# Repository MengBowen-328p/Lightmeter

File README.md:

# CW32_Lightmeter

# Timeline

## 2023.9.2:Finished SCH
## 2023.9.4:Finished PCB Layout

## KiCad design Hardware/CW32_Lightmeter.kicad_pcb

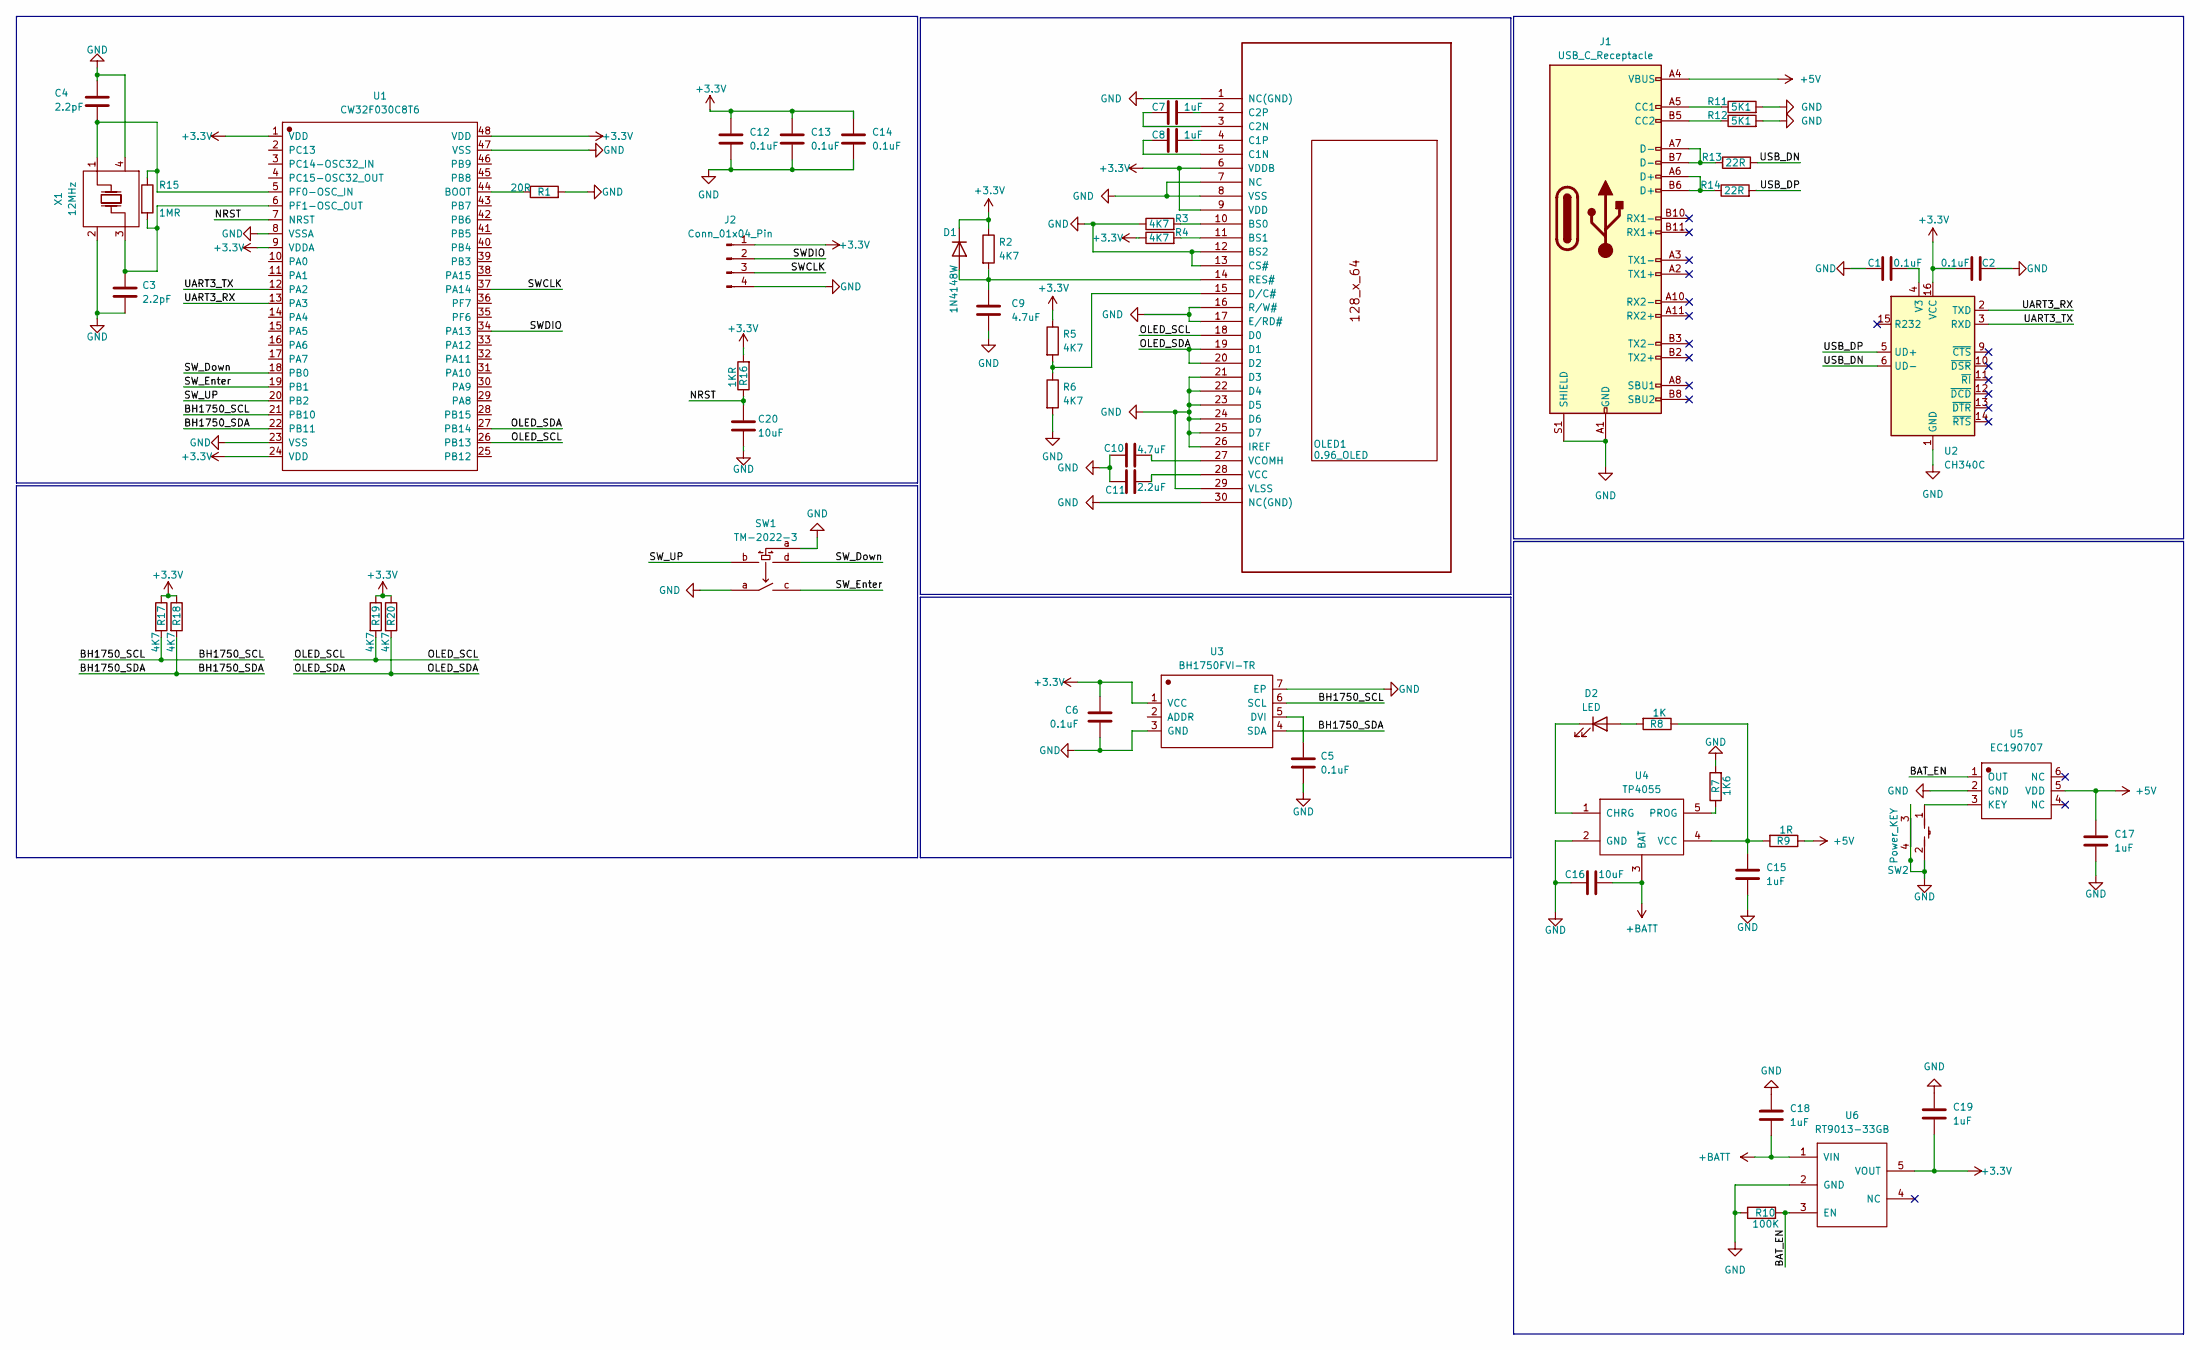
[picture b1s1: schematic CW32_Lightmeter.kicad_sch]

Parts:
C1, C2, C5, C6, C12, C13, C14: 0.1uF; C_0603_1608Metric
C3, C4: 2.2pF; C_0603_1608Metric
C7, C8, C15, C17, C18, C19: 1uF; C_0603_1608Metric
C9, C10: 4.7uF; C_0603_1608Metric
C11: 2.2uF; C_0603_1608Metric
C16, C20: 10uF; C_0603_1608Metric
D1: 1N4148W; D_SOD-123
D2: LED; LED_0603_1608Metric
J1: USB_C_Receptacle; USB_C_Receptacle_GCT_USB4105-xx-A_16P_TopMnt_Horizontal
J2: Conn_01x04_Pin; SWD_Port
OLED1: 0.96_OLED; OLED_0.96-30P-P0.70-12864
R1: 20R; R_0603_1608Metric
R2, R3, R4, R5, R6, R17, R18, R19, R20: 4K7; R_0603_1608Metric
R7: 1K6; R_0603_1608Metric
R8: 1K; R_0603_1608Metric
R9: 1R; R_0603_1608Metric
R10: 100K; R_0603_1608Metric
R11, R12: 5K1; R_0603_1608Metric
R13, R14: 22R; R_0603_1608Metric
R15: 1MR; R_0603_1608Metric
R16: 1KR; R_0603_1608Metric
SW1: TM-2022-3; SW-SMD_TM-2022-3
SW2: Power_KEY; SW-SMD_2X4X3.5MM
U1: CW32F030C8T6; LQFP-48_L7.0-W7.0-P0.50-LS9.0-BL
U2: CH340C; SOIC-16_3.9x9.9mm_P1.27mm
U3: BH1750FVI-TR; WSOF-6_L2.6-W1.6-P0.50-TL-EP
U4: TP4055; SOT-23-5_L3.0-W1.7-P0.95-LS2.8-BR
U5: EC190707; PG-SOT23-6_L2.9-W1.6-P0.95-LS2.8-BR
U6: RT9013-33GB; SOT-23-5_L3.0-W1.7-P0.95-LS2.8-BL
X1: 12MHz; CRYSTAL-SMD_4P-L3.2-W2.5-BL

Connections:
+3.3V: C2.2, C6.2, C12.1, C13.1, C14.1, C19.2, D1.1 (K), J2.1, OLED1.6 (VDDB), OLED1.9 (VDD), R2.1, R4.1, R5.1, R16.2, R17.1, R18.1, R19.1, R20.1, U1.1 (VDD), U1.9 (VDDA), U1.24 (VDD), U1.48 (VDD), U2.16 (VCC), U3.1 (VCC), U6.5 (VOUT)
+5V: C17.1, J1.A4 (VBUS), J1.A9 (VBUS), J1.B4 (VBUS), J1.B9 (VBUS), R9.1, U5.5 (VDD)
+BATT: C16.2, C18.2, U4.3 (BAT), U6.1 (VIN)
/BAT_EN: R10.2, U5.1 (OUT), U6.3 (EN)
/BH1750_SCL: R17.2, U1.21 (PB10), U3.6 (SCL)
/BH1750_SDA: R18.2, U1.22 (PB11), U3.4 (SDA)
/NRST: C20.1, R16.1, U1.7 (NRST)
/OLED_SCL: OLED1.18 (D0), R19.2, U1.26 (PB13)
/OLED_SDA: OLED1.19 (D1), OLED1.20 (D2), R20.2, U1.27 (PB14)
/SWCLK: J2.3, U1.37 (PA14)
/SWDIO: J2.2, U1.34 (PA13)
/SW_Down: SW1.d, U1.18 (PB0)
/SW_Enter: SW1.c, U1.19 (PB1)
/SW_UP: SW1.b, U1.20 (PB2)
/UART3_RX: U1.13 (PA3), U2.2 (TXD)
/UART3_TX: U1.12 (PA2), U2.3 (RXD)
/USB_DN: R13.2, U2.6 (UD-)
/USB_DP: R14.2, U2.5 (UD+)
GND: C1.1, C2.1, C3.2, C4.1, C5.2, C6.1, C9.2, C10.1, C11.1, C12.2, C13.2, C14.2, C15.2, C16.1, C17.2, C18.1, C19.1, C20.2, J1.A1 (GND), J1.A12 (GND), J1.B1 (GND), J1.B12 (GND), J1.S1 (SHIELD), J2.4, OLED1.1 (NC(GND)), OLED1.7 (NC), OLED1.8 (VSS), OLED1.12 (BS2), OLED1.13 (CS#), OLED1.16 (R/W#), OLED1.17 (E/RD#), OLED1.21 (D3), OLED1.22 (D4), OLED1.23 (D5), OLED1.24 (D6), OLED1.25 (D7), OLED1.26 (IREF), OLED1.29 (VLSS), OLED1.30 (NC(GND)), R1.2, R3.1, R6.2, R7.2, R10.1, R11.2, R12.2, SW1.a, SW2.2, SW2.3, SW2.4, U1.8 (VSSA), U1.23 (VSS), U1.47 (VSS), U2.1 (GND), U3.3 (GND), U3.7 (EP), U4.2 (GND), U5.2 (GND), U6.2 (GND), X1.2 (GND), X1.4 (GND)
unnamed: C9.1, D1.2 (A), OLED1.14 (RES#), R2.2
unnamed: D2.2 (A), R8.2
unnamed: D2.1 (K), U4.1 (CHRG)
unnamed: J1.A5 (CC1), R11.1
unnamed: J1.B5 (CC2), R12.1
unnamed: J1.A6 (D+), J1.B6 (D+), R14.1
unnamed: J1.A7 (D-), J1.B7 (D-), R13.1
unnamed: OLED1.10 (BS0), R3.2
unnamed: OLED1.11 (BS1), R4.2
unnamed: C8.1, OLED1.5 (C1N)
unnamed: C8.2, OLED1.4 (C1P)
unnamed: C7.1, OLED1.3 (C2N)
unnamed: C7.2, OLED1.2 (C2P)
unnamed: OLED1.15 (D/C#), R5.2, R6.1
unnamed: C11.2, OLED1.28 (VCC)
unnamed: C10.2, OLED1.27 (VCOMH)
unnamed: R1.1, U1.44 (BOOT)
unnamed: C4.2, R15.1, U1.5 (PF0-OSC_IN), X1.1 (OSC1)
unnamed: C3.1, R15.2, U1.6 (PF1-OSC_OUT), X1.3 (OSC2)
unnamed: C1.2, U2.4 (V3)
unnamed: C5.1, U3.5 (DVI)
unnamed: R7.1, U4.5 (PROG)
unnamed: C15.1, R8.1, R9.2, U4.4 (VCC)
unnamed: SW2.1, U5.3 (KEY)

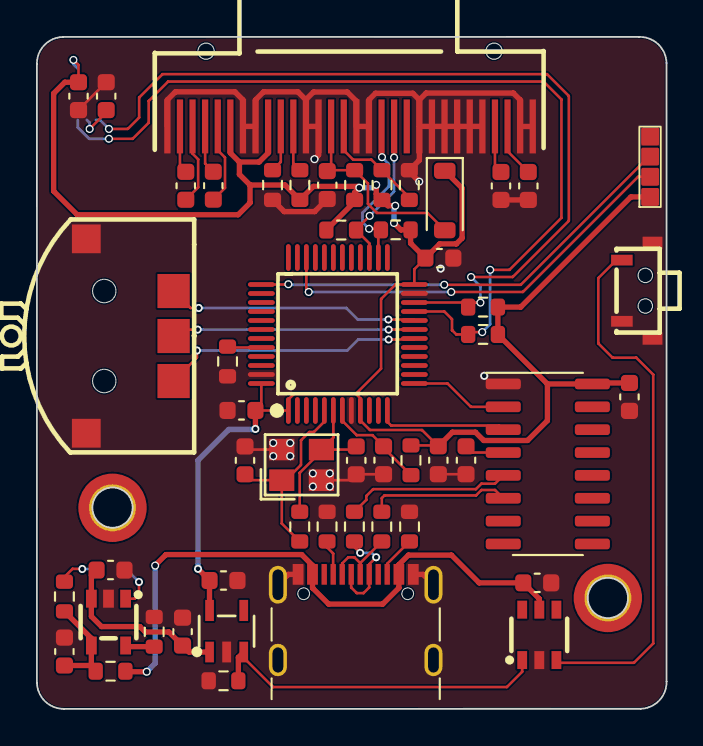
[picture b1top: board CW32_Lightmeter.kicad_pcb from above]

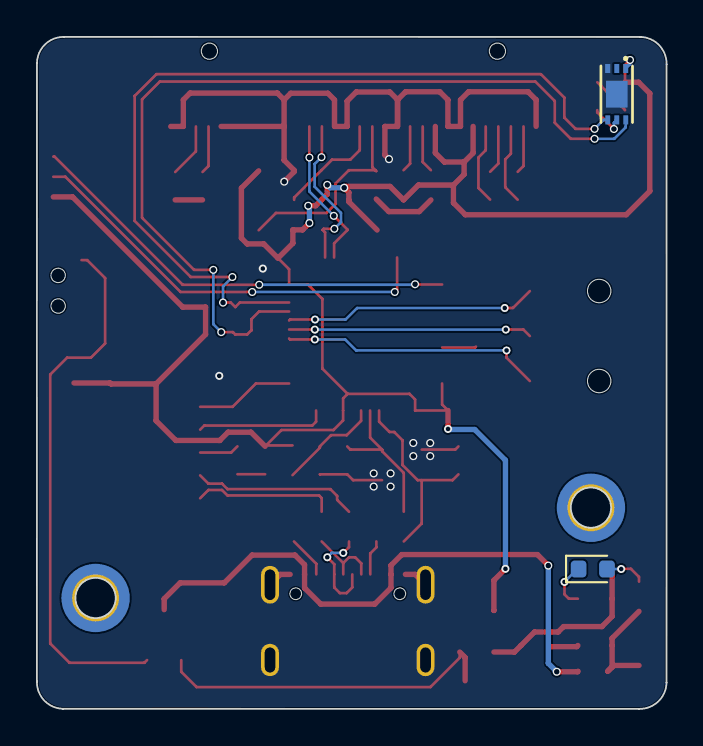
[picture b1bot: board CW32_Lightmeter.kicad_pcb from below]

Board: 2 copper layers, 35.0 x 37.3 mm, 54 parts (2 on the bottom side), 43 nets.

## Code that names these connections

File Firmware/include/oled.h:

//
// Created by 15216 on 2023/11/17.
//

#ifndef FIRMWARE_OLED_H
#define FIRMWARE_OLED_H

#include <Arduino.h>
#include <Wire.h>
#include <U8g2lib.h>

#define OLED_SCL_PIN PB14
#define OLED_SDA_PIN PB13

class OLED
{
public:
    void oledInit(void);
    void showStartScreen(void);
    void showMainMenu(uint8_t menu_page);
    void showLuxMenu(void);
    void showNDMenu(void);
};

#endif //FIRMWARE_OLED_H

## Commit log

2023-09-02 Update SCH
2023-09-03 Update PCB Layout
2023-09-04 Finished PCB Layout
2023-09-05 Hardware Finished
2023-09-12 Finsished PCB Layout
2023-10-05 Update Switch Driver
2023-10-08 Update I2C
2023-11-16 Refactor By Arduino
2023-11-19 Update Button
2023-11-19 Update Class Index
2023-11-20 Update Index
2023-11-22 Update Some UI
